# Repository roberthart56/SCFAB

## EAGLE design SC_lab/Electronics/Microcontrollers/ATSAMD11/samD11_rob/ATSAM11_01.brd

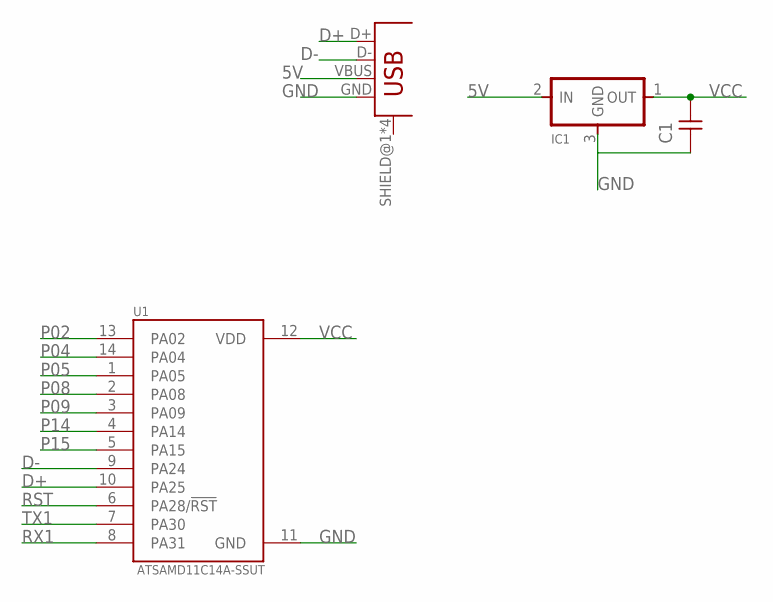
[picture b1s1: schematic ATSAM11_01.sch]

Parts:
C1: CAP-UNPOLARIZED; C1206
IC1: VR_REGULATOR-SOT23SOT23; SOT23
U1: ATSAMD11C14A-SSUT; SOIC127P600X160-14N
U$1: CONN_USB_MINIB; USB_MINIB

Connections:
5V: IC1.2 (IN), U$1.VBUS
D+: U1.10 (PA25), U$1.D+
D-: U1.9 (PA24), U$1.D-
GND: C1.1, IC1.3 (GND), U1.11 (GND), U$1.GND
P02: U1.13 (PA02)
P04: U1.14 (PA04)
P05: U1.1 (PA05)
P08: U1.2 (PA08)
P09: U1.3 (PA09)
P14: U1.4 (PA14)
P15: U1.5 (PA15)
RST: U1.6 (PA28/!RST)
RX1: U1.8 (PA31)
TX1: U1.7 (PA30)
VCC: C1.2, IC1.1 (OUT), U1.12 (VDD)

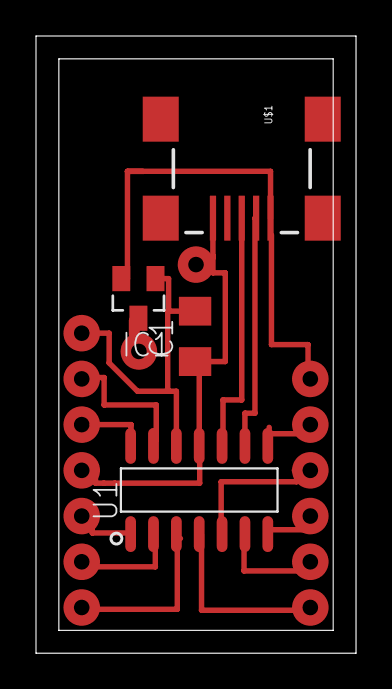
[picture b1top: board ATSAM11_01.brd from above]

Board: 2 copper layers, 17.8 x 34.3 mm, 4 parts (0 on the bottom side), 5 nets.

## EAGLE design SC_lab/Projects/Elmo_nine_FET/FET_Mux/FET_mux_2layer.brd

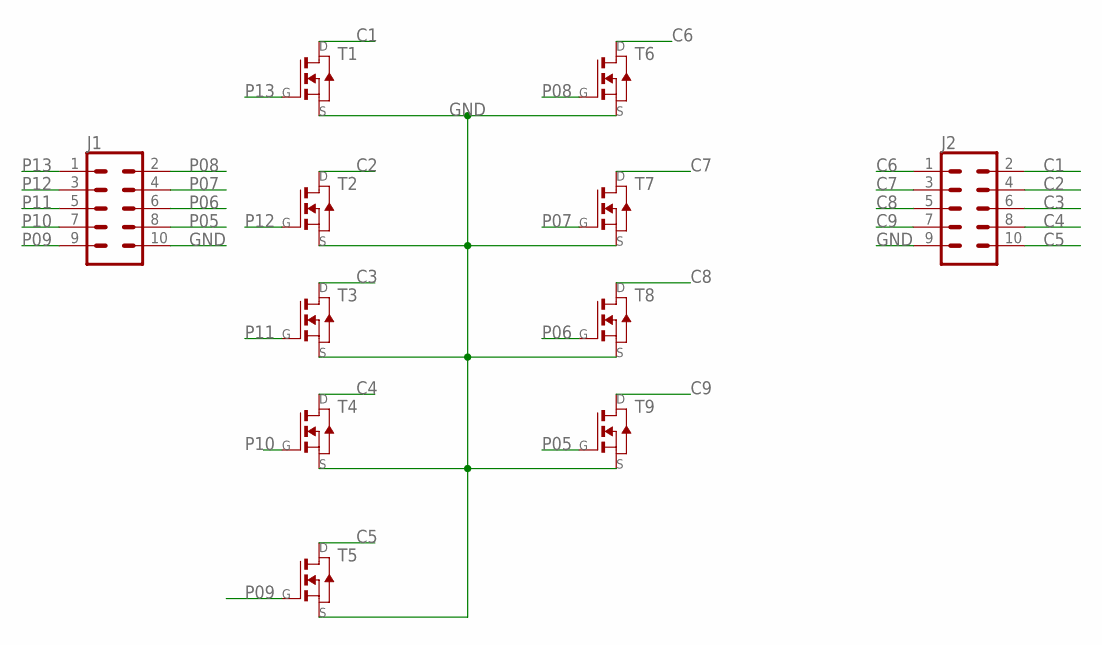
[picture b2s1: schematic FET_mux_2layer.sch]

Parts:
J1, J2: CONN_05X2SHD_SMD; 2X5-SHROUDED_SMD
T1, T2, T3, T4, T5, T6, T7, T8, T9: NMOSFETSOT23; SOT-23

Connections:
C1: J2.2, T1.1 (D)
C2: J2.4, T2.1 (D)
C3: J2.6, T3.1 (D)
C4: J2.8, T4.1 (D)
C5: J2.10, T5.1 (D)
C6: J2.1, T6.1 (D)
C7: J2.3, T7.1 (D)
C8: J2.5, T8.1 (D)
C9: J2.7, T9.1 (D)
GND: J1.10, J2.9, T1.2 (S), T2.2 (S), T3.2 (S), T4.2 (S), T5.2 (S), T6.2 (S), T7.2 (S), T8.2 (S), T9.2 (S)
P05: J1.8, T9.3 (G)
P06: J1.6, T8.3 (G)
P07: J1.4, T7.3 (G)
P08: J1.2, T6.3 (G)
P09: J1.9, T5.3 (G)
P10: J1.7, T4.3 (G)
P11: J1.5, T3.3 (G)
P12: J1.3, T2.3 (G)
P13: J1.1, T1.3 (G)

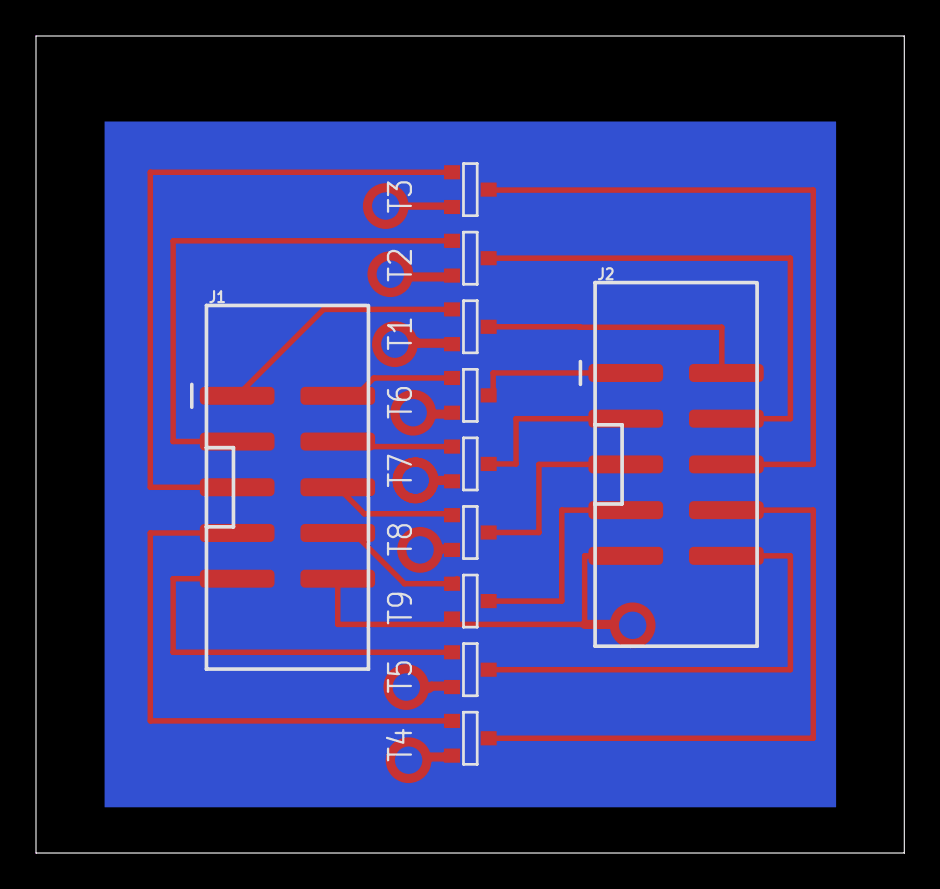
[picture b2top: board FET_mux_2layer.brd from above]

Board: 2 copper layers, 48.2 x 45.4 mm, 11 parts (0 on the bottom side), 19 nets.

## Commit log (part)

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2019-06-12 button files
2019-06-12 edit code for buttons
2019-06-12 button edits
2019-06-12 edits
2019-06-12 modify programs
2019-06-18 edit events
2019-06-21 added links to class
2019-06-21 electronics edit
2019-06-21 add to electronics
2019-06-27 elect. basics edits
2019-06-28 rev. tools
2019-07-01 Add tools
2019-07-03 added pics and edited indexlhtml for light pen project
2019-07-03 added quick prototypes
2019-07-03 update FET
2019-07-18 sensor edits
2019-07-18 rx-tx edits
2019-07-19 composit adding and editing
2019-07-22 add layup pics and text
2019-07-23 output dev. edits
2019-07-23 edit motors, composites
2019-07-23 edit protoboard project
2019-07-24 added protboard pics and text
2019-07-24 output dev
2019-07-25 edit protoboard
2019-07-29 add radio project
2019-07-29 edit radio files
2019-07-29 added fetmux project
2019-07-30 add molding
2019-07-31 edit fet files
2019-08-05 edit fet project
2019-08-07 tools edits
2019-08-26 Add HTMAA2019
2019-08-29 add calendar
2019-08-29 Add soldering to tools
2019-09-01 add lab furniture folder
2019-09-10 tools edit
2019-09-11 added circuitboard page
2019-09-11 edits on circuitboard
2019-09-18 modify figure
2019-09-19 add circuitboard instr.
2019-09-19 edit and add processes for milling
2019-09-20 replace tools folder
2019-10-08 add shopbot
2019-10-10 link shopbot, edit shopbot
2019-12-02 update projects
2019-12-03 add 2020 class
2019-12-03 add to PS70
2020-01-08 add stepper project
2020-01-08 comment code.
2020-01-09 added sketcher code
2020-01-14 Add ATSAM documentation
2020-01-14 links fo board files for stepper
2020-01-21 add m0 and m4 files
2020-01-21 recover files for M4 nrf
2020-01-26 added tools info.
2020-01-29 revise electronics intro
2020-01-30 add fles to atsam11
2020-02-05 add inkscape
2020-02-05 inkscape info.
2020-02-05 add inkscape page
2020-02-06 Inkscape page edit
2020-02-06 laser cutter info.
2020-02-06 edit instructions
2020-02-06 add gimp info.
2020-02-11 soldering
2020-02-13 DS files.
2020-02-17 junk
2020-02-17 change electronics
2020-02-17 edit link
2020-02-17 electronics edits and additions
2020-02-17 add samd14 info
2020-02-18 microcontroller add and edit
2020-02-18 links to boards
2020-02-18 ADD ADAFRUIT
2020-02-18 motor-coupler
2020-02-18 ds store
2020-02-20 arduino addts.
2020-02-20 edit arduino
2020-02-20 arduino edits.
2020-02-20 added feather pinout
2020-02-20 correct figure name
2020-02-26 sensor additions and edits
2020-03-03 add stepper file
2020-03-03 add code and update html
2020-03-05 capacitive and other sensor
2020-03-06 capacitance edits
2020-03-23 edit fet page
2020-03-23 correct names
2020-03-24 add led files
2020-03-24 add vanna info
2020-03-24 resize pics
2020-03-25 microcontroller edits and additions for SAMD11
2020-03-25 micro upjdates
2020-03-25 output devices edits
2020-03-26 add h-bridge tutorial to page.
2020-03-26 ste[[er nstructions
2020-03-27 stepper additions
2020-03-27 navigation links added
2020-03-28 add stepper stuff
2020-03-28 edit stepper
2020-03-30 rearrange netwroking
2020-03-30 networking additions
2020-03-30 add uart
2020-03-30 add to networking
2020-03-30 networking and samd11
2020-03-31 repair pic link?
2020-03-31 radios
2020-03-31 fixed links
2020-03-31 radio edits
2020-04-01 add esp32
2020-04-01 edit radio
2020-04-01 radio additions
2020-04-01 update stepper
2020-04-01 Create pot_send_Huzzah32
2020-04-01 Update pot_send_Huzzah32
2020-04-03 motor board examples
2020-04-07 networking - internet
2020-04-07 edit firebase app
2020-04-10 add pinouts
2020-04-10 added navigation
2020-04-13 machine week
2020-04-14 machine edits
2020-04-16 additions to machine
2020-04-20 added code for steppers
2020-04-20 motor driver additions
2020-04-20 stepper edits
2020-04-21 move and add machine demo stuff
2020-04-21 machine addtns
2020-04-21 add machine exps
2020-04-21 edit achines
2020-04-23 add machine code tutorial
2020-04-28 add python machine
2020-05-18 various adds in networking
2020-05-18 add ESP NOW stuff
2020-05-19 add 3d design
2020-05-20 add accelerometers
2020-05-22 added stl and linked machine
2020-06-03 add kit pics
2020-06-15 add rotating trap
2020-06-15 add pics to saddle folder
2020-06-17 Thermistor folder adder
2020-06-18 add matl. to trap project
2020-06-19 added paper and edit index
2020-06-19 added project doc
2020-06-22 temp and thermistor
2020-06-23 add navigation, button index
2020-06-23 add 50springs
2020-06-29 reorganize
2020-06-30 new saddle file
2020-06-30 added sewing2020
2020-07-01 electronic basics edits
2020-07-07 modify button
2020-07-07 Add Huzzah index.html
2020-07-07 add phototrans info
2020-07-13 add sensors
2020-07-13 capacitance
2020-07-13 add stepper links
2020-07-14 edit mag sensor
2020-07-14 add thermistor pics
2020-07-15 update steppers
2020-07-15 update wired networking
2020-07-15 edits on uart example
2020-07-16 update ESPnow
2020-07-16 add machine page s-12
2020-07-17 work on s-12 machine
2020-07-17 drawling machine
2020-07-17 add to machine
2020-07-20 networking adds
2020-07-21 edit machine code
2020-07-21 edit pics and code for machine.
2020-07-23 links tomachine
2020-07-29 Sound updates
2020-09-09 add vis2233
    add vis2233
2020-09-16 Add arduio workshop
2020-09-18 rotating trap updates
2020-09-23 add photoresistor material to VIS2233
2020-09-23 add page on vision
2020-09-29 add demo files
2020-09-30 edite vis2233
2020-10-06 add firebase
2020-10-14 demo of stepper
2020-10-21 add touch
2020-10-21 add code
2020-10-22 replace touch-stepper
2020-10-28 add dc motor
2020-10-28 transistor adds
2020-11-03 add saddle stuff
2020-11-13 edit machines s12
2020-11-16 measurements Nov16
2020-12-02 add data on saddle
2020-12-07 saddle update
2020-12-08 add dec7 jpynb
2020-12-08 added jupiter notebook
2020-12-09 saddle edits
2020-12-09 add saddle pic
2020-12-11 added data
2020-12-14 add figure
2021-01-09 add notebook html
2021-01-09 add pdf
2021-01-13 add jan12 data
2021-01-13 move pynb
2021-01-13 added saddle height files
2021-01-13 notebook changes
2021-01-19 add plots and data
2021-01-21 lots of adds
2021-01-21 edit md for saddle
2021-01-21 added picture of plot
2021-01-21 edit
2021-01-26 edit saddle
2021-01-26 edit nb.md
2021-01-27 new stl
2021-02-03 new data
2021-02-03 data add
2021-02-03 edit readme
2021-02-09 data feb 9
2021-02-25 add data
2021-02-25 edit filename
2021-11-09 added step resp
